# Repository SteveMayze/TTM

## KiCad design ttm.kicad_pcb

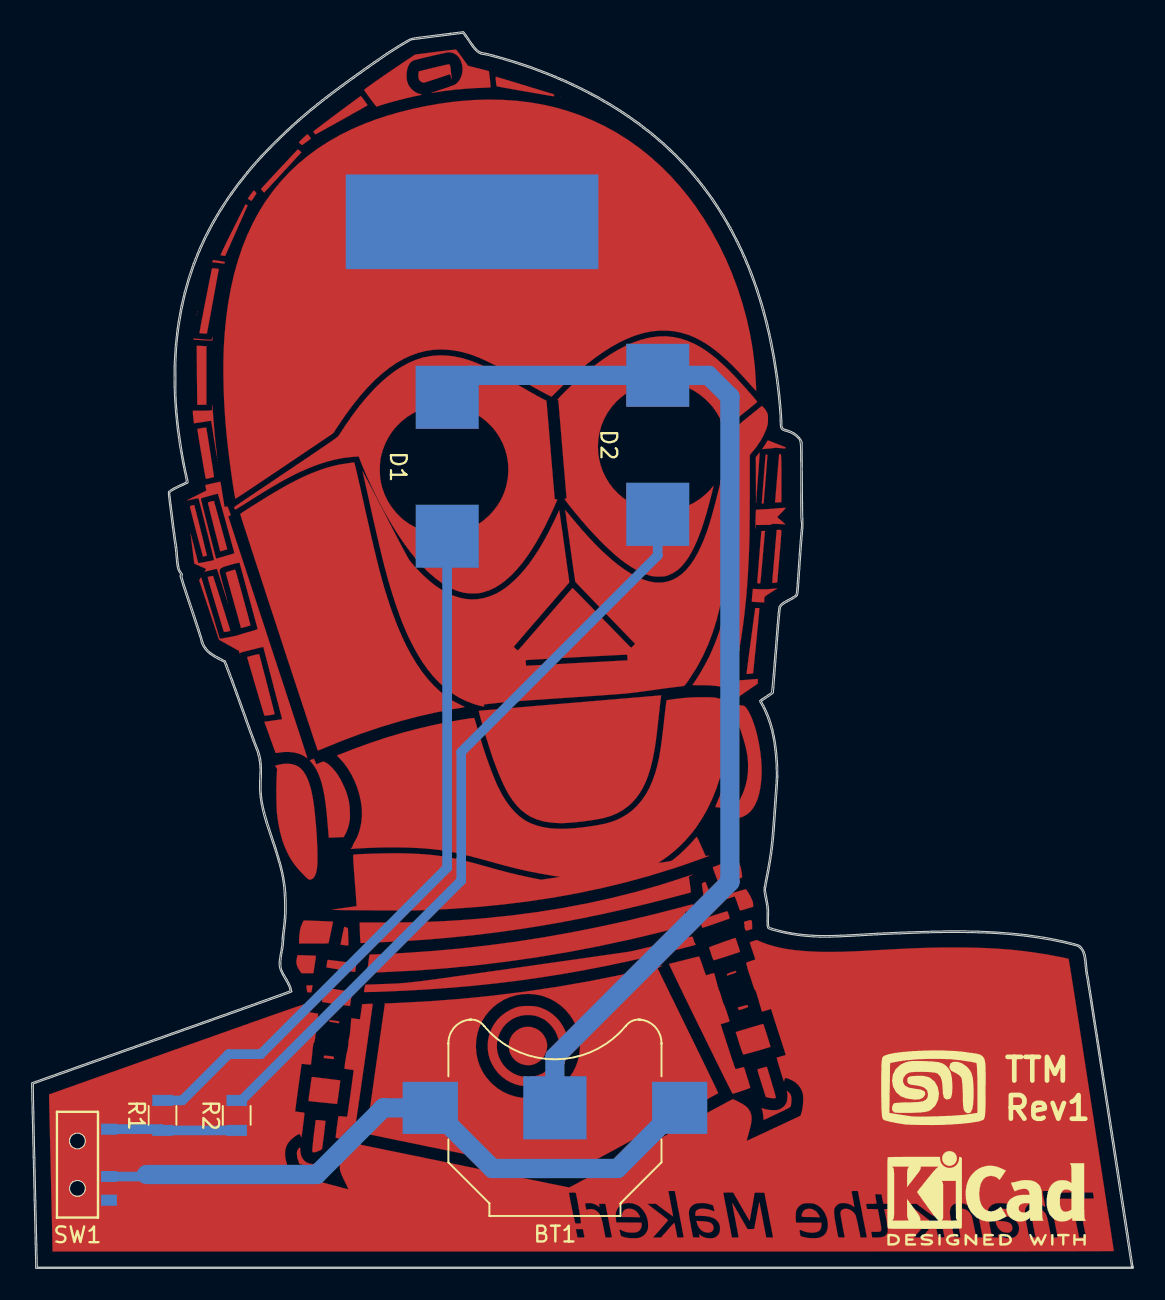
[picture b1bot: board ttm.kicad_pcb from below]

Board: 2 copper layers, 69.8 x 78.3 mm, 10 parts (8 on the bottom side), 5 nets.

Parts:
BT1: Battery_Cell; BatteryHolder_Keystone_3000_1x12mm
D1, D2: LED; LY_T77K_NH
Edge Cut: LOGO; c3po_EdgeCut
Front CU Text: LOGO; c3po_FCu_Text
KiCAD_Logo: KiCad-Logo2_6mm_SilkScreen
R1, R2: R; R_0805
SM_Logo: LOGO; MyBasic_rounded_50_1
SW1: SW_SPDT; Micro_Schiebeschalter

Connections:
unnamed: BT1.1, SW1.2
unnamed: BT1.2, D1.1, D2.1
unnamed: D1.2, R1.2
unnamed: D2.2, R2.2
unnamed: R1.1, R2.1, SW1.1

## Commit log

2021-05-29 Recovered repository
